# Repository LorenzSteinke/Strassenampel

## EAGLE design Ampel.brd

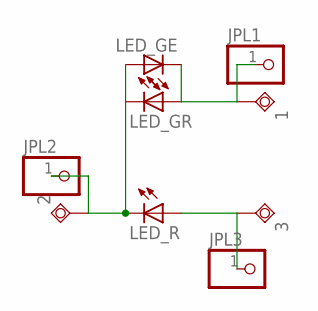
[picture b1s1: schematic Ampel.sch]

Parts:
1: 1; TP10SQ
2: 2; TP10SQ
3: 3; TP10SQ
JPL1, JPL2, JPL3: PINHD-1X1KL; 1X01_KL
LED_GE: LEDCHIP_-LED0402; CHIP-LED0402
LED_GR: LEDCHIP_-LED0402; CHIP-LED0402
LED_R: LEDCHIP_-LED0402; CHIP-LED0402

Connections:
unnamed: 1.TP, JPL1.1, LED_GE.C, LED_GR.A
unnamed: 2.TP, JPL2.1, LED_GE.A, LED_GR.C, LED_R.C
unnamed: 3.TP, JPL3.1, LED_R.A

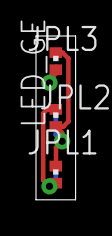
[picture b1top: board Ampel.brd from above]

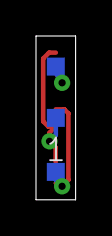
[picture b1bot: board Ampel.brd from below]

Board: 2 copper layers, 2.2 x 9.1 mm, 9 parts (3 on the bottom side), 3 nets.

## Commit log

2020-01-24 Druckvorlagen fuer Verkehrsampeln
